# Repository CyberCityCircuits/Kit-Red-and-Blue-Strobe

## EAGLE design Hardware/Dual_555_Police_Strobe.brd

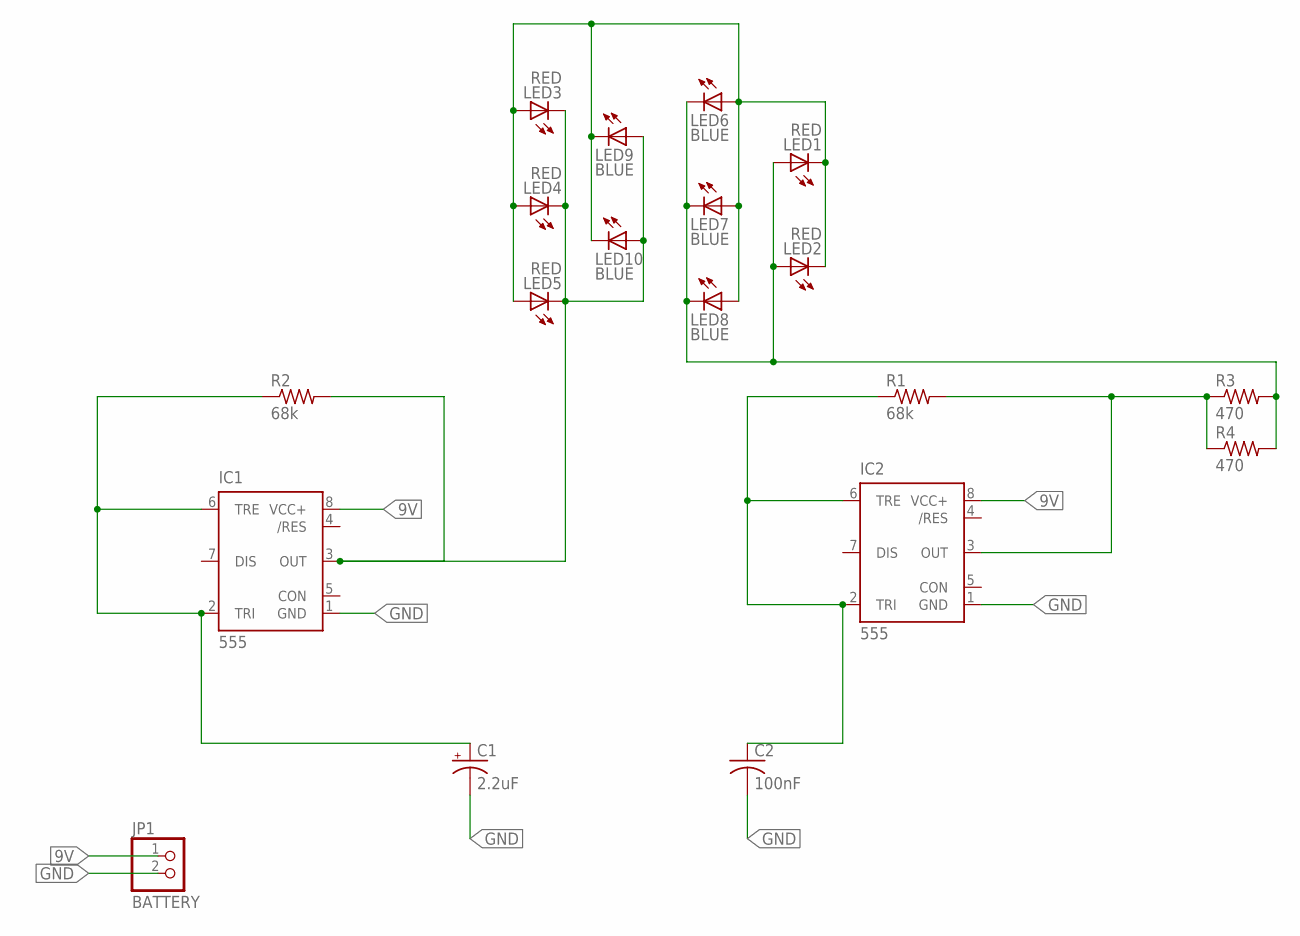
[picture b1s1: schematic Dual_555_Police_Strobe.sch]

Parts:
C1: 2.2uF; E2,5-6
C2: 100nF; C025-050X050
IC1, IC2: 555; DIP08
JP1: BATTERY; 1X02
LED1, LED2, LED3, LED4, LED5: RED; LED5MM
LED6, LED7, LED8, LED9, LED10: BLUE; LED5MM
R1, R2: 68k; 0207/10
R3, R4: 470; 0207/10

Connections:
9V: IC1.8 (VCC+), IC2.8 (VCC+), JP1.1
GND: C1.-, C2.2, IC1.1 (GND), IC2.1 (GND), JP1.2
unnamed: C1.+, IC1.2 (TRI), IC1.6 (TRE), R2.1
unnamed: C2.1, IC2.2 (TRI), IC2.6 (TRE), R1.1
unnamed: IC1.3 (OUT), LED3.K (C), LED4.K (C), LED5.K (C), LED9.A, LED10.A, R2.2
unnamed: LED1.A, LED2.A, LED6.K (C), LED7.K (C), LED8.K (C), R3.2, R4.2
unnamed: IC2.3 (OUT), R1.2, R3.1, R4.1
unnamed: LED1.K (C), LED2.K (C), LED3.A, LED4.A, LED5.A, LED6.A, LED7.A, LED8.A, LED9.K (C), LED10.K (C)

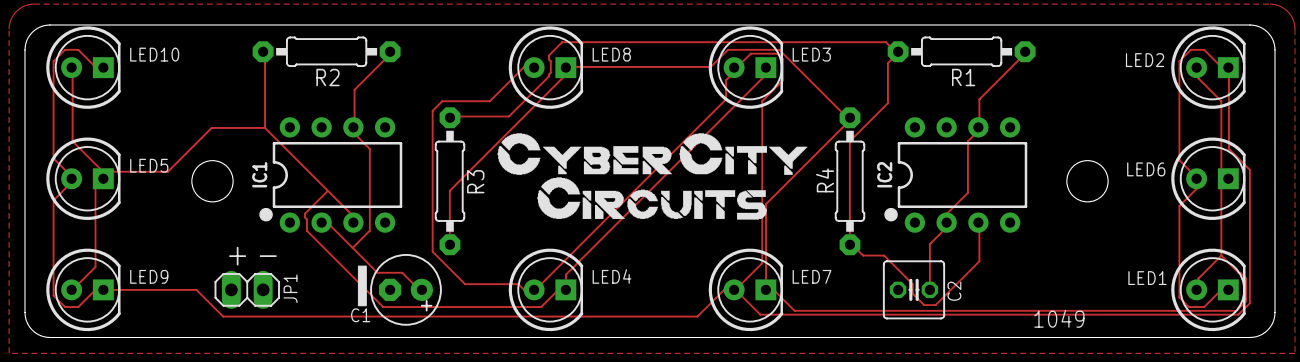
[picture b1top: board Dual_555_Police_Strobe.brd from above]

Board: 2 copper layers, 100.0 x 25.0 mm, 19 parts (0 on the bottom side), 8 nets.

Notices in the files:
parts and their libraries:
SparkFun-IC-Special-Function: Licensing: Creative Commons ShareAlike 4.0 International - https://creativecommons.org/licenses/by-sa/4.0
